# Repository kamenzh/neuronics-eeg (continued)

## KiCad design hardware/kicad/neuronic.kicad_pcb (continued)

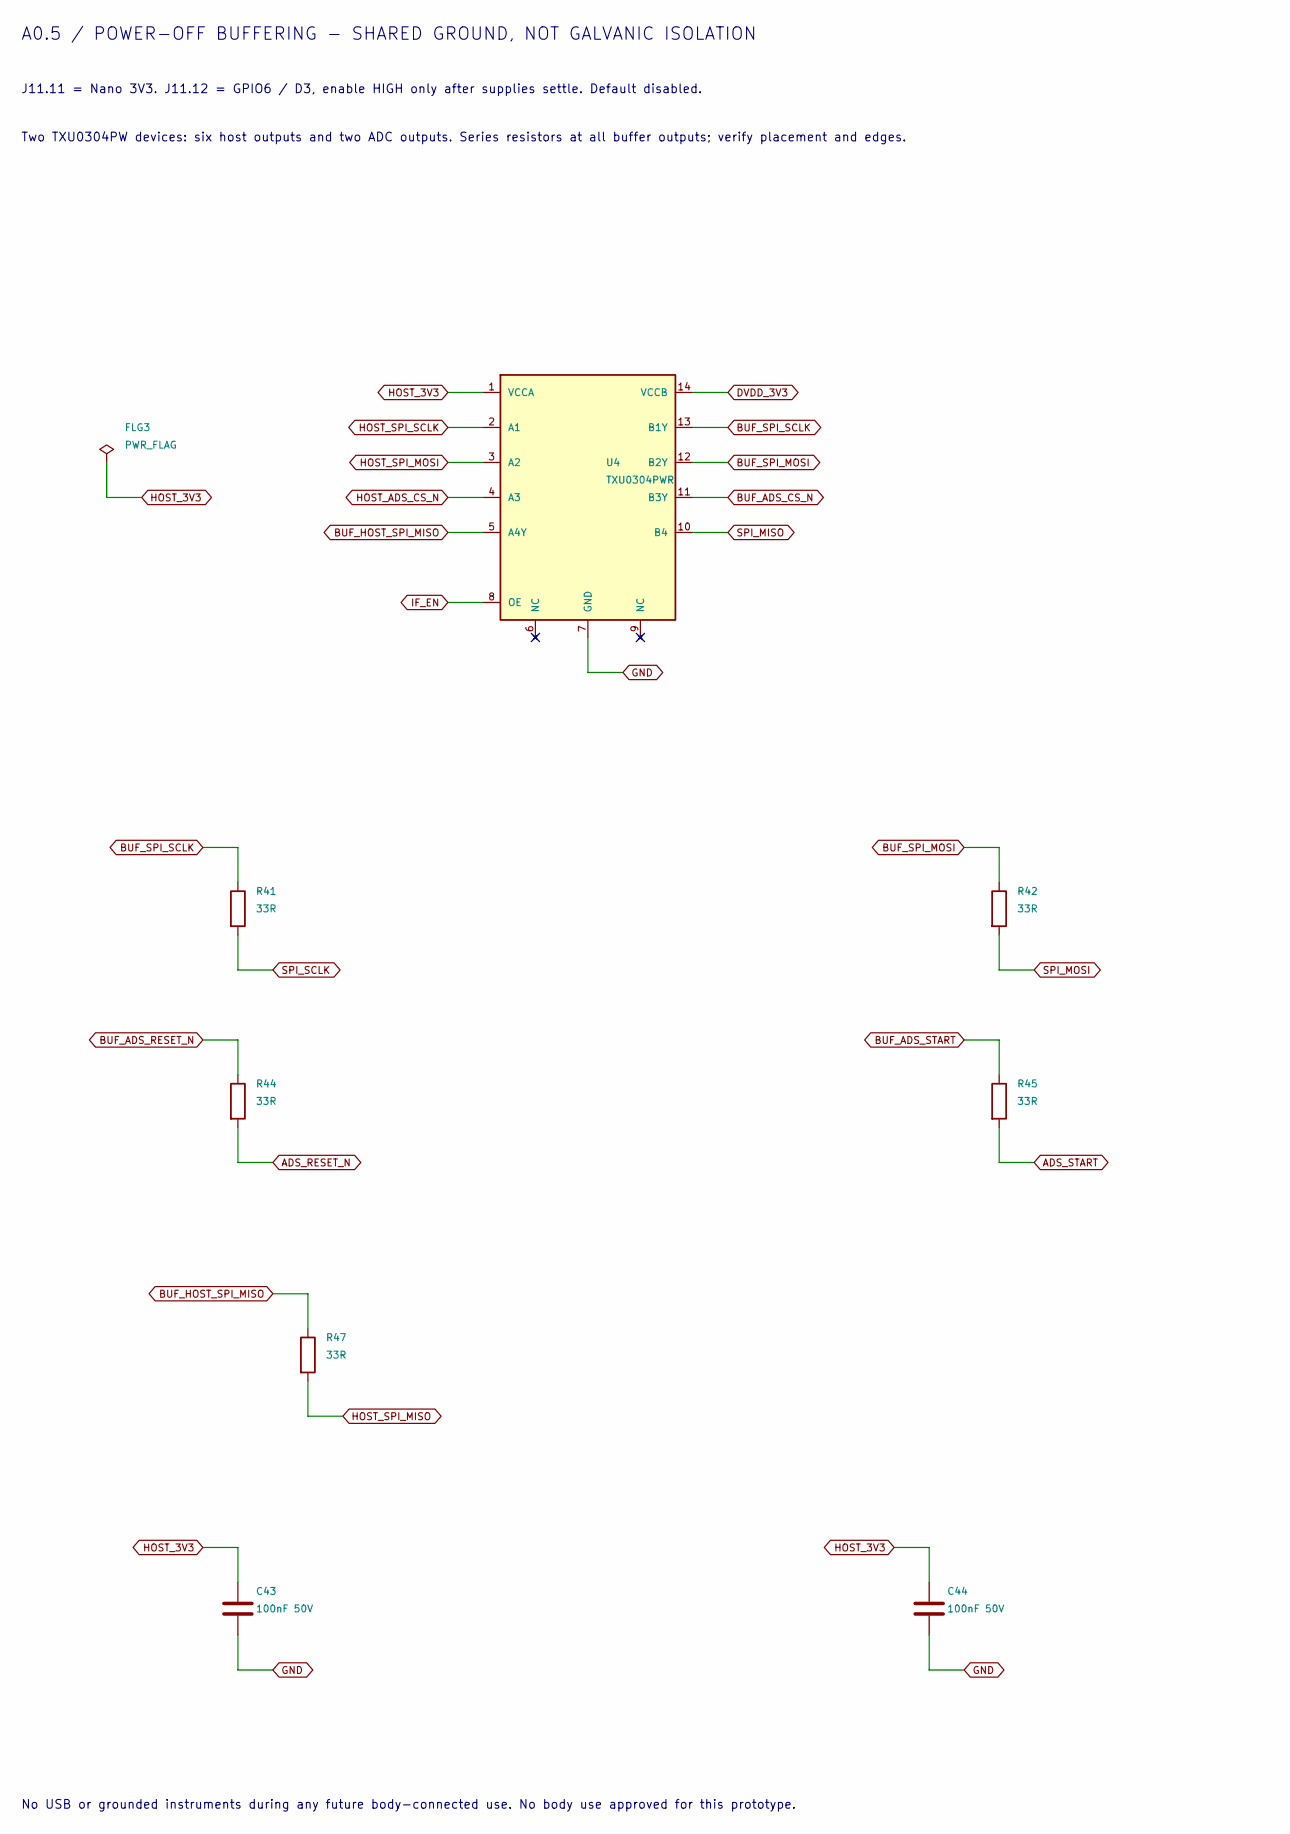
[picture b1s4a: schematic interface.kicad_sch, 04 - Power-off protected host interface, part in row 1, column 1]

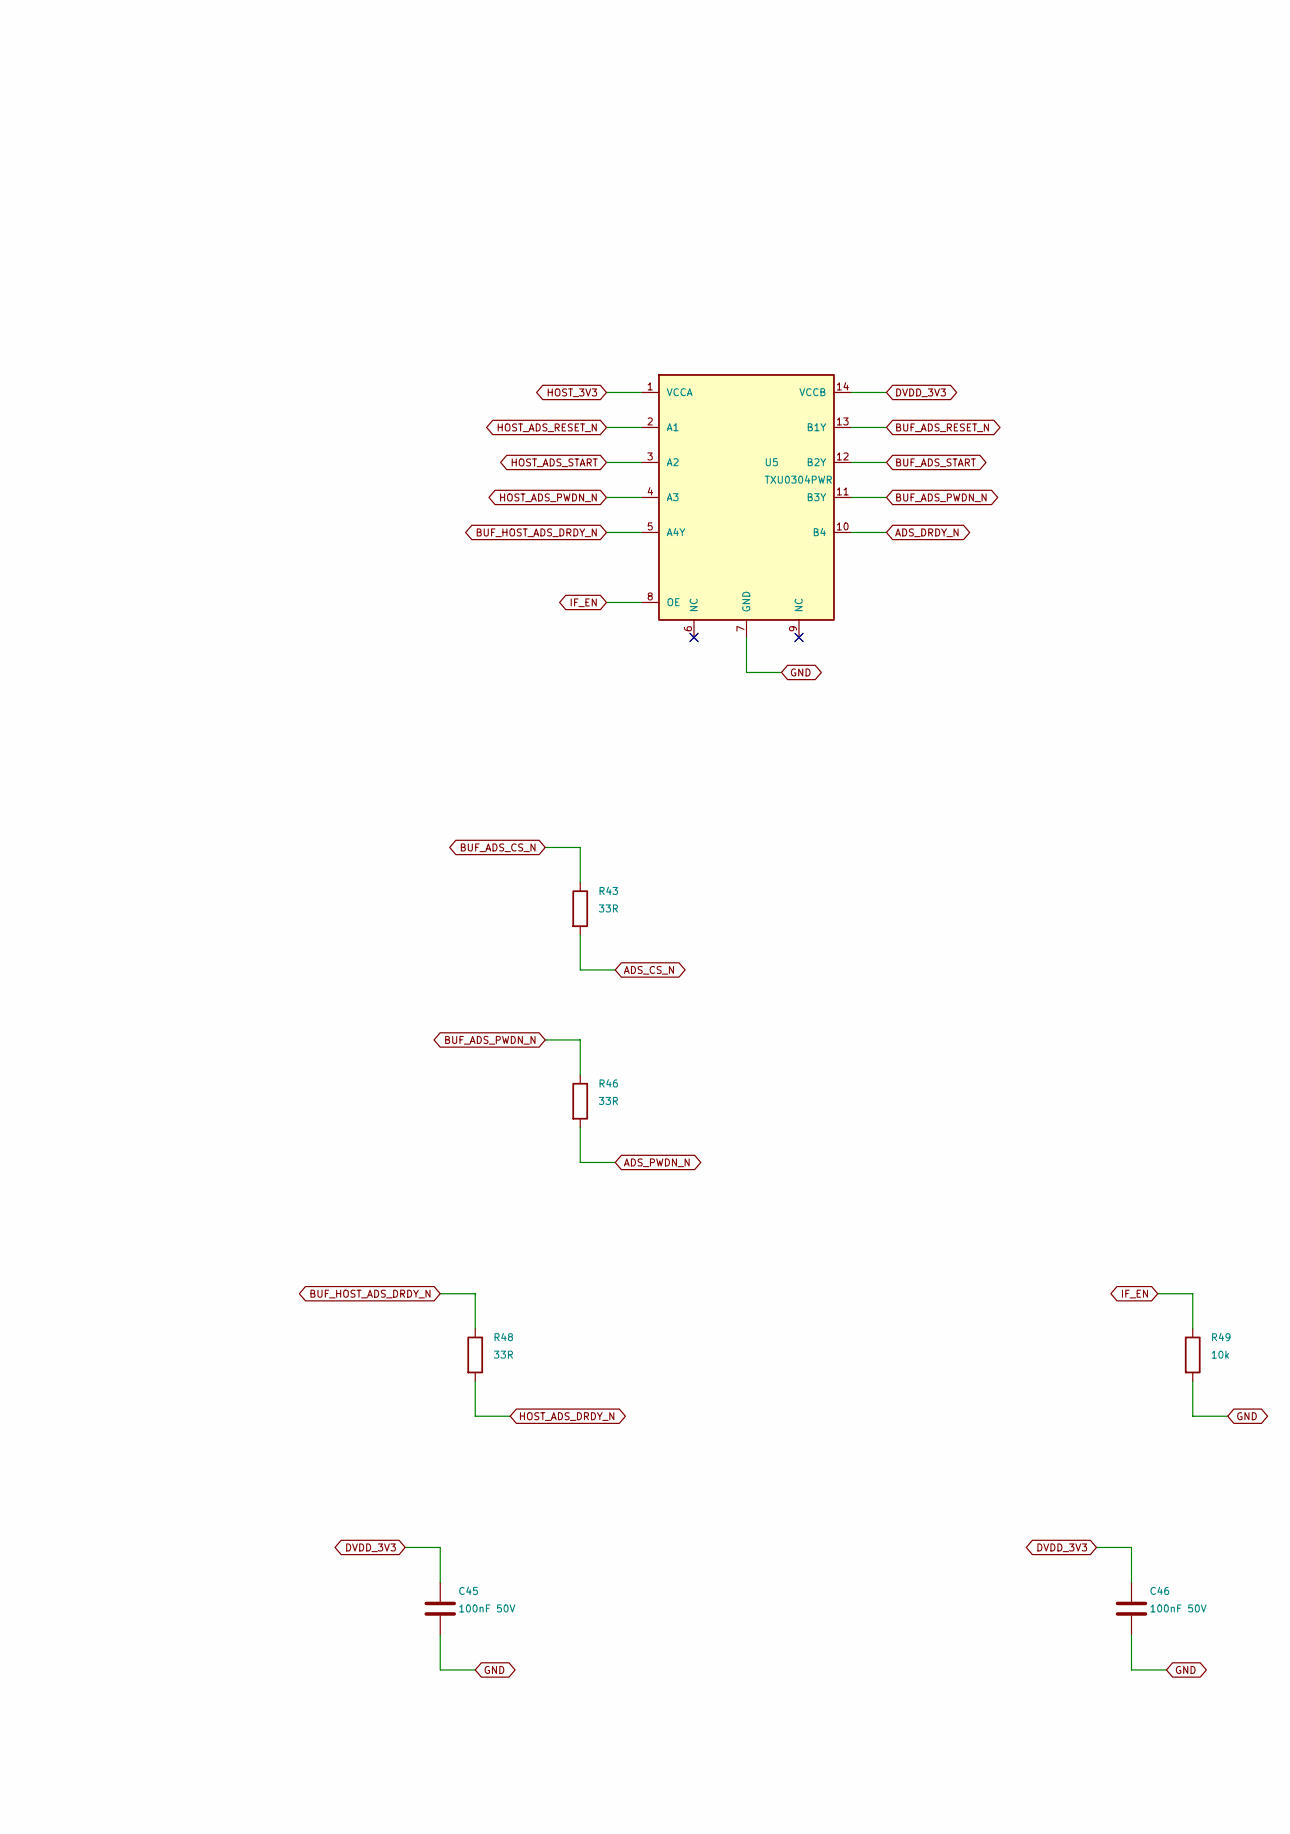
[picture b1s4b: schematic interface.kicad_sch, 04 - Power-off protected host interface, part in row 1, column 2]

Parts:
C43, C44, C45, C46: 100nF 50V; C_0805_2012Metric
FLG3: PWR_FLAG
R41, R42, R43, R44, R45, R46, R47, R48: 33R; R_0805_2012Metric
R49: 10k; R_0805_2012Metric
U4, U5: TXU0304PWR; TSSOP-14_4.4x5mm_P0.65mm

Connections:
ADS_CS_N: R43.2; also elsewhere on the board
ADS_DRDY_N: U5.10 (B4); also elsewhere on the board
ADS_PWDN_N: R46.2; also elsewhere on the board
ADS_RESET_N: R44.2; also elsewhere on the board
ADS_START: R45.2; also elsewhere on the board
BUF_ADS_CS_N: R43.1, U4.11 (B3Y)
BUF_ADS_PWDN_N: R46.1, U5.11 (B3Y)
BUF_ADS_RESET_N: R44.1, U5.13 (B1Y)
BUF_ADS_START: R45.1, U5.12 (B2Y)
BUF_HOST_ADS_DRDY_N: R48.1, U5.5 (A4Y)
BUF_HOST_SPI_MISO: R47.1, U4.5 (A4Y)
BUF_SPI_MOSI: R42.1, U4.12 (B2Y)
BUF_SPI_SCLK: R41.1, U4.13 (B1Y)
DVDD_3V3: C45.1, C46.1, U4.14 (VCCB), U5.14 (VCCB); also elsewhere on the board
GND: C43.2, C44.2, C45.2, C46.2, R49.2, U4.7 (GND), U5.7 (GND); also elsewhere on the board
HOST_3V3: C43.1, C44.1, FLG3.1, U4.1 (VCCA), U5.1 (VCCA); also elsewhere on the board
HOST_ADS_CS_N: U4.4 (A3); also elsewhere on the board
HOST_ADS_DRDY_N: R48.2; also elsewhere on the board
HOST_ADS_PWDN_N: U5.4 (A3); also elsewhere on the board
HOST_ADS_RESET_N: U5.2 (A1); also elsewhere on the board
HOST_ADS_START: U5.3 (A2); also elsewhere on the board
HOST_SPI_MISO: R47.2; also elsewhere on the board
HOST_SPI_MOSI: U4.3 (A2); also elsewhere on the board
HOST_SPI_SCLK: U4.2 (A1); also elsewhere on the board
IF_EN: R49.1, U4.8 (OE), U5.8 (OE); also elsewhere on the board
SPI_MISO: U4.10 (B4); also elsewhere on the board
SPI_MOSI: R42.2; also elsewhere on the board
SPI_SCLK: R41.2; also elsewhere on the board

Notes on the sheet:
A0.5 / POWER-OFF BUFFERING - SHARED GROUND, NOT GALVANIC ISOLATION
J11.11 = Nano 3V3. J11.12 = GPIO6 / D3, enable HIGH only after supplies settle. Default disabled.
Two TXU0304PW devices: six host outputs and two ADC outputs. Series resistors at all buffer outputs; verify placement and edges.
No USB or grounded instruments during any future body-connected use. No body use approved for this prototype.

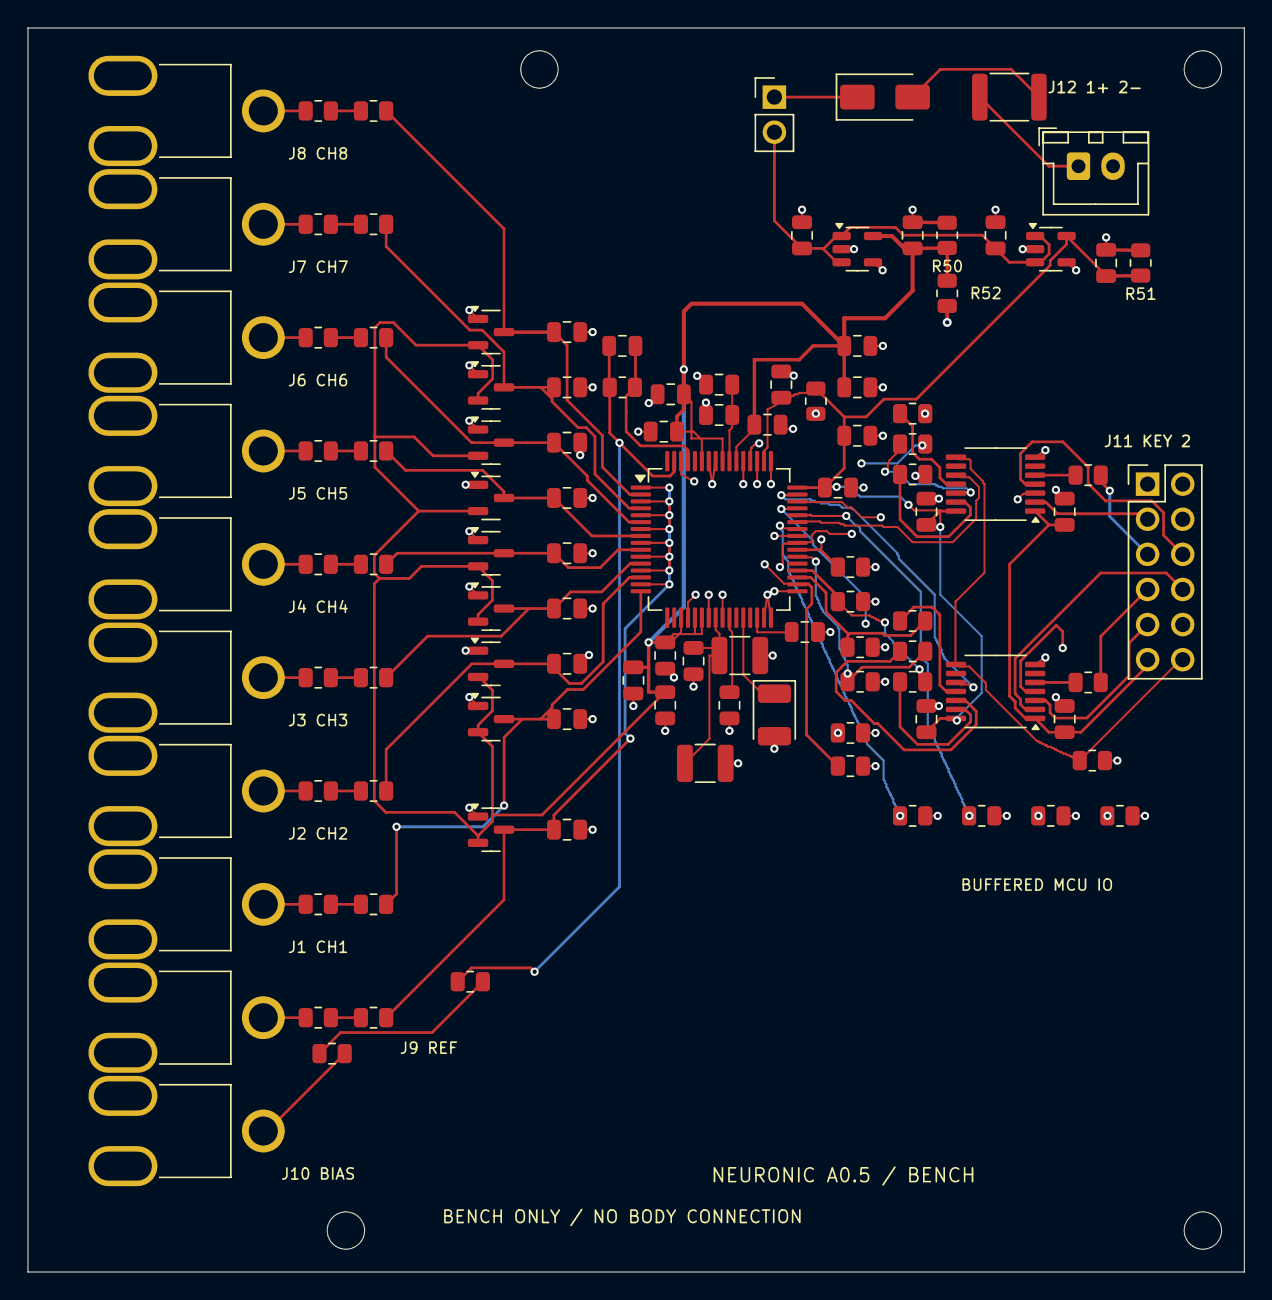
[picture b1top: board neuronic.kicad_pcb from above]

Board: 4 copper layers, 88.0 x 90.0 mm, 114 parts (0 on the bottom side), 74 nets.

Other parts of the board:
H1, H2, H3, H4: M2.5; MountingHole_2.7mm_M2.5

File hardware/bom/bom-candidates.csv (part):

References,Quantity,Manufacturer,Candidate_MPN,Specification,Footprint,Source,Review_status,Notes
R36 R37 R38 R39 R40,5,Yageo,RC0805FR-0710KL,"10 kohm, 1%, 0805, 0.125W",Neuronic:R_0805_2012Metric,https://yageogroup.com/component-documentation/download/spec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,candidate_not_order_release,Check pulse/fault stress and excess noise in final analog design
R30 R31 R32 R33 R34 R35,6,Yageo,RC0805FR-0710KL,"10k, 1%, 0805, 0.125W",Neuronic:R_0805_2012Metric,https://yageogroup.com/component-documentation/download/spec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,candidate_not_order_release,10k gives <=0.122V for 12uA combined ADC/buffer leakage; verify host startup and rail sequencing
R20,1,Yageo,RC0805FR-071ML,"1 Mohm, 1%, 0805, 0.125W",Neuronic:R_0805_2012Metric,https://yageogroup.com/component-documentation/download/spec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,candidate_not_order_release,Check pulse/fault stress and excess noise in final analog design
R21 R22,2,Yageo,RC0805FR-07499KL,"499 kohm, 1%, 0805, 0.125W",Neuronic:R_0805_2012Metric,https://yageogroup.com/component-documentation/download/spec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,candidate_not_order_release,Check pulse/fault stress and excess noise in final analog design
C10,1,KEMET,C0805C152J5GACTU,"1.5nF, 5%, 50V, C0G, 0805",Neuronic:C_0805_2012Metric,https://search.kemet.com/component-documentation/download/sp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,candidate_not_order_release,Verify effective capacitance at operating bias/temperature and aging; nominal value alone is insufficient
C25 C26 C28 C31 C32 C33 C34 C35 C36 C39 C40,11,KEMET,C0805C105K3RACTU,"1uF, 10%, 25V, X7R, 0805",Neuronic:C_0805_2012Metric,https://search.kemet.com/component-documentation/download/sp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,candidate_not_order_release,Verify effective capacitance at operating bias/temperature and aging; nominal value alone is insufficient
C27 C30 C38 C41 C43 C44 C45 C46,8,KEMET,C0805C104K5RACTU,"100nF, 10%, 50V, X7R, 0805",Neuronic:C_0805_2012Metric,https://search.kemet.com/component-documentation/download/sp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,candidate_not_order_release,Verify effective capacitance at operating bias/temperature and aging; nominal value alone is insufficient
C20 C22 C23 C21,4,KEMET,C0805C475K3RACTU,"4.7uF, 10%, 25V, X7R, 0805",Neuronic:C_0805_2012Metric,https://search.kemet.com/component-documentation/download/sp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,candidate_not_order_release,Verify effective capacitance at operating bias/temperature and aging; nominal value alone is insufficient
C37,1,KEMET,C0805C106K3PACTU,"10uF, 10%, 25V, X5R, 0805",Neuronic:C_0805_2012Metric,https://search.kemet.com/component-documentation/download/sp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,candidate_not_order_release,Verify effective capacitance at operating bias/temperature and aging; nominal value alone is insufficient
C29 C42,2,KEMET,C1210C226K3RACTU,"22uF, 10%, 25V X7R, 1210; two fitted in parallel",Neuronic:C_1210_3225Metric,https://search.kemet.com/component-documentation/download/sp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,candidate_not_order_release,Two fitted. Manufacturer typical DC-bias curve inspected; bounded design estimate >20uF combined. Physical operating-value/startup verification still required.
C24,1,KEMET,T491B107M006AT,"100uF, 20%, 6.3V, tantalum, B/3528-21",Neuronic:CP_EIA-3528-21_Kemet-B,https://search.kemet.com/component-documentation/download/sp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,candidate_not_order_release,Polarized: pad1 VCAP1 positive; verify leakage/startup/surge and derating for this internal rail
U1,1,Texas Instruments,ADS1299IPAG,"8 channels, TQFP64/PAG, 0.5mm pitch",Neuronic:TQFP-64_10x10mm_P0.5mm,https://www.ti.com/lit/ds/symlink/ads1299.pdf,candidate_not_order_release,ADS1299IPAGR is reel packaging of the same PAG device; one IC total
U2,1,Texas Instruments,TPS7A2450DBVR,"5 V fixed, 18 V input, 200 mA, SOT-23-5",Neuronic:SOT-23-5,https://www.ti.com/lit/ds/symlink/tps7a24.pdf,candidate_not_order_release,"Pin 1 IN, 2 GND, 3 EN tied to IN, 4 NC tied GND for thermal performance, 5 OUT. 2% combined accuracy budget. Measure rail noise/startup/reverse-current behavior."
U3,1,Texas Instruments,TPS7A2433DBVR,"3.3 V fixed, 18 V input, 200 mA, SOT-23-5",Neuronic:SOT-23-5,https://www.ti.com/lit/ds/symlink/tps7a24.pdf,candidate_not_order_release,"Pin 1 IN, 2 GND, 3 EN tied to IN, 4 NC tied GND for thermal performance, 5 OUT. 2% combined accuracy budget. Measure rail noise/startup/reverse-current behavior."
D1 D2 D3 D4 D5 D6 D7 D8 D9,9,Nexperia,"BAV199,215","Dual series low leakage diode, SOT-23",Neuronic:SOT-23,https://assets.nexperia.com/documents/data-sheet/BAV199.pdf,candidate_not_order_release,Not a proven ADS1299 absolute-maximum clamp or body-protection solution
D10,1,Vishay,SS14-E3/61T,"40V, 1A Schottky, SMA",Neuronic:D_SMA,https://www.vishay.com/docs/88746/ss12.pdf,candidate_not_order_release,Check forward drop at AFE load and reverse leakage
F1,1,Bourns,MF-MSMF014-2,"1812, 60 V, 0.14 A hold / 0.34 A trip at 23 C",Neuronic:Fuse_1812_4532Metric,https://www.bourns.com/docs/product-datasheets/mf-msmf.pdf,candidate_not_order_release,
J12,1,JST,B2B-XH-A(LF)(SN),"2-pin, 2.50mm, vertical XH",Neuronic:JST_XH_B2B-XH-A_1x02_P2.50mm_Vertical,https://www.jst-mfg.com/product/pdf/eng/eXH.pdf,candidate_not_order_release,Harness requires matching XHP-2 housing and wire-appropriate contacts; do not infer polarity from wire color
J11,1,Wurth Elektronik,61301221121,"2x6, 2.54mm, vertical male header",Neuronic:PinHeader_2x06_P2.54mm_Vertical,https://www.we-online.com/components/products/datasheet/6130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,candidate_not_order_release,A0.5 keyed harness: pad 2 isolated. Remove exposed pin 2 and plug matching socket cavity. Only pin 1 is signal ground.
J1 J2 J3 J4 J5 J6 J7 J8 J9 J10,10,P1 Technologies,8R003661901F,36619 black right-angle PCB jack; 1.5 mm touchproof DIN 42802 Type BU,Neuronic:P1_36619_Touchproof_RA,https://catalog.p1tec.com/?FILTER_CLEAR=&FILTER_FCOMPONENT=36619,candidate_not_order_release,A0.3: signal finished hole 2.10mm; isolated dummy plated slots 4.20x2.10mm. See tolerance worksheet; sample fit and fabricator slot confirmation required.
SW1,1,Wurth Elektronik,61300211121,"1x2, 2.54mm header for offboard SPST switch",Neuronic:PinHeader_1x02_P2.54mm_Vertical,https://www.we-online.com/components/products/datasheet/6130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,candidate_not_order_release,"This MPN buys the PCB header, not the external switch"
U4 U5,2,Texas Instruments,TXU0304PWR,"3 A-to-B + 1 B-to-A buffer, dual supply, Ioff/VCC disconnect, TSSOP-14",Neuronic:TSSOP-14_4.4x5mm_P0.65mm,https://www.ti.com/lit/ds/symlink/txu0304.pdf,candidate_not_order_release,"A=host 3.3V, B=AFE 3.3V, OE controlled on J11.12. Common ground; NOT galvanic isolation."
R41 R42 R43 R44 R45 R46 R47 R48,8,Yageo,RC0805FR-0733RL,"33 ohm, 1%, 0805",Neuronic:R_0805_2012Metric,https://www.yageo.com/en/Chart/Download/pdf/RC0805.pdf,candidate_not_order_release,Source damping at buffer outputs; not a safety current limiter.
R49,1,Yageo,RC0805FR-0710KL,"10k, 1%, 0805",Neuronic:R_0805_2012Metric,https://www.yageo.com/en/Chart/Download/pdf/RC0805.pdf,candidate_not_order_release,Buffer OE default disabled.
R51,1,Yageo,RC0805FR-071KL,"1 kohm, 1%, 0805, 0.125W",Neuronic:R_0805_2012Metric,https://yageogroup.com/component-documentation/download/spec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,candidate_not_order_release,Passive regulator-output discharge load.
R1 R2 R3 R4 R5 R6 R7 R8 R9 R10 R11 R12 R13 R14 R15 R16 R17 R18,18,Yageo,RT0805BRD07100KL,"100 kohm, 0.1%, 25 ppm/K, 0805",Neuronic:R_0805_2012Metric,https://www.yageogroup.com/component-documentation/download/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,candidate_not_order_release,Two independent series resistors per contact.
R50 R52,2,Yageo,RC0805FR-07499RL,"499 ohm, 1%, 0805, 0.125 W",Neuronic:R_0805_2012Metric,https://www.yageogroup.com/component-documentation/download/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,candidate_not_order_release,"Parallel analog rail bleeds, individually rated for the full rail voltage."
C1 C2 C3 C4 C5 C6 C7 C8,8,KEMET,C0805C471F5GACTU,"470 pF, 1%, 50 V, C0G, 0805",Neuronic:C_0805_2012Metric,https://yageogroup.com/download/specsheet/C0805C471F5GACTU,candidate_not_order_release,C9 is tuned separately for the shared reference. Verify actual common-mode response.
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
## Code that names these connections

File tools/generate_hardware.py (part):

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    '23':'AVSS', '24':'VREFP', '25':'VREFN', '26':'VCAP4', '27':'NC', '28':'VCAP1',
    '29':'NC', '30':'VCAP2', '31':'RESV1', '32':'AVSS', '33':'DGND', '34':'DIN',
    '35':'~{PWDN}', '36':'~{RESET}', '37':'CLK', '38':'START', '39':'~{CS}', '40':'SCLK',
    '41':'DAISY_IN', '42':'GPIO1', '43':'DOUT', '44':'GPIO2', '45':'GPIO3', '46':'GPIO4',
    '47':'~{DRDY}', '48':'DVDD', '49':'DGND', '50':'DVDD', '51':'DGND', '52':'CLKSEL',
    '53':'AVSS1', '54':'AVDD1', '55':'VCAP3', '56':'AVDD', '57':'AVSS', '58':'AVSS',
    '59':'AVDD', '60':'BIASREF', '61':'BIASINV', '62':'BIASIN', '63':'BIASOUT', '64':'RESERVED'}
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        typ = 'input'
        if name.startswith(('AVDD','AVSS','DVDD','DGND')): typ='power_in'
        elif name in ['DOUT','~{DRDY}','BIASOUT'] or name.startswith('VCAP'): typ='output'
        elif name.startswith('GPIO') or name in ['SRB1','SRB2','VREFP','BIASINV']: typ='bidirectional'
        elif name in ['NC','RESERVED']: typ='no_connect'
        pins.append((str(i), name, typ, -22.86 if side else 22.86, y, 0 if side else 180))
    LIB['Neuronic:ADS1299IPAG'] = custom_symbol('ADS1299IPAG', pins, 20.32, 43.18,
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    nets.update({'17':None,'18':None,'19':'AVDD_5V','20':'GND','21':'AVDD_5V','22':'AVDD_5V','23':'GND',
        '24':'VREFP','25':'GND','26':'VCAP4','27':None,'28':'VCAP1','29':None,'30':'VCAP2','31':'GND','32':'GND',
        '33':'GND','34':'SPI_MOSI','35':'ADS_PWDN_N','36':'ADS_RESET_N','37':None,'38':'ADS_START','39':'ADS_CS_N',
        '40':'SPI_SCLK','41':'GND','42':'GPIO1_PD','43':'SPI_MISO','44':'GPIO2_PD','45':'GPIO3_PD','46':'GPIO4_PD',
        '47':'ADS_DRDY_N','48':'DVDD_3V3','49':'GND','50':'DVDD_3V3','51':'GND','52':'CLKSEL_PU',
        '53':'GND','54':'AVDD_5V','55':'VCAP3','56':'AVDD_5V','57':'GND','58':'GND','59':'AVDD_5V',
        '60':None,'61':'BIASINV','62':'GND','63':'BIASOUT','64':None})
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    root.text('Waveshare ESP32-S3-Nano; see hardware/interface.json.',258,100)
    root.text('External controller power/USB can join GND. No body-connected tests.',258,107)
    rnum=30
    for i,(net,rail) in enumerate([('ADS_CS_N','GND'),('ADS_RESET_N','GND'),('ADS_PWDN_N','GND'),('ADS_START','GND'),('SPI_SCLK','GND'),('SPI_MOSI','GND'),('CLKSEL_PU','DVDD_3V3'),('GPIO1_PD','GND'),('GPIO2_PD','GND'),('GPIO3_PD','GND'),('GPIO4_PD','GND')]):
        x=35+(i%6)*58;y=181+(i//6)*40
        add_rc(root,f'R{rnum+i}','10k',net,rail,x,y,(116+(i%4)*5,103+(i//4)*7))
    root.text('Default pulldowns keep ADC controls low at startup. MCU must release PWDN/RESET and drive CS high after rails settle.',20,250)
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
    power.text('BENCH POWER: 6 x AA alkaline candidate (7.2-10.2 V review envelope) -> 5 V / 3.3 V LDOs',18,17,1.8)
    power.text('ESP32 has its own supply. No onboard charging. Regulators must not supply ESP32 radio current.',18,25)
    power.part('J12','Connector_Generic:Conn_01x02','BATTERY_6AA',40,48,{'1':'VBAT_RAW','2':'GND'},'Neuronic:JST_XH_B2B-XH-A_1x02_P2.50mm_Vertical',xy=(132,66),note='Candidate keyed battery connector; pin 1 positive, pin 2 ground; verify harness polarity')
    power.part('F1','Device:Polyfuse','140mA_HOLD',100,48,{'1':'VBAT_RAW','2':'VBAT_FUSED'},'Neuronic:Fuse_1812_4532Metric',xy=(124,60),note='MF-MSMF014-2: 60V, 140mA hold / 340mA trip at 23C; AFE branch only, not body protection',mpn='MF-MSMF014-2')
    power.part('D10','Device:D_Schottky','SS14',162,48,{'2':'VBAT_FUSED','1':'VBAT_DIODE'},'Neuronic:D_SMA',xy=(117,60),note='Reverse polarity protection; verify thermal behavior',mpn='SS14')
    power.part('SW1','Switch:SW_SPST','POWER',220,48,{'1':'VBAT_DIODE','2':'VBAT'},'Neuronic:PinHeader_1x02_P2.54mm_Vertical',xy=(109,60),note='Header for an offboard SPST switch')
    for i,(value,rail) in enumerate([('TPS7A2450DBVR','AVDD_5V'),('TPS7A2433DBVR','DVDD_3V3')]):
        power.part(f'U{i+2}','Neuronic:TPS7A24_FIXED',value,95+155*i,86,{'1':'VBAT','2':'GND','3':'VBAT','4':'GND','5':rail},'Neuronic:SOT-23-5',xy=(109+i*14,72),note='Fixed DBV: 1 VIN, 2 GND, 3 EN=VIN, 4 NC=GND, 5 VOUT',mpn=value)
    add_rc(power,'R50','499R','AVDD_5V','GND',330,86,(116.5,70),rot=90)
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
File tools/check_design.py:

#!/usr/bin/env python3
"""Audit the actual KiCad-exported netlist against the source and pin contract.

Not a replacement for ERC, DRC, analog review or physical measurements.
"""
import json
import sys
import xml.etree.ElementTree as ET
from pathlib import Path

ROOT=Path(__file__).resolve().parents[1]
src=json.loads((ROOT/'hardware/design.json').read_text())
tree=ET.parse(ROOT/'hardware/validation/neuronic.net.xml').getroot()
comps={x.attrib['ref']:x for x in tree.findall('components/comp')}
actual={}
for net in tree.findall('nets/net'):
    for node in net.findall('node'):
        actual[(node.attrib['ref'],node.attrib['pin'])]=net.attrib['name']
checks=[]
def check(name,condition):
    checks.append({'name':name,'passed':bool(condition)})
    if not condition: print('FAIL:',name)

parts={p['ref']:p for p in src['parts']}
check('All 110 physical components exported by KiCad',set(parts)==set(comps) and len(parts)==110)
for p in parts.values():
    check(f"{p['ref']} footprint matches schematic",comps[p['ref']].findtext('footprint')==p['fp'])
    for pin,net in p['nets'].items():
        found=actual.get((p['ref'],pin),'')
        check(f"{p['ref']}.{pin} -> {net or 'NC'}",found==net if net else found.startswith('unconnected-') or not found)

# This physical pin contract is deliberately independent of the generator's map.
pin_contract={
    '16':'EEG1','14':'EEG2','12':'EEG3','10':'EEG4','8':'EEG5','6':'EEG6','4':'EEG7','2':'EEG8',
    '1':'REF_FILTERED','3':'REF_FILTERED','5':'REF_FILTERED','7':'REF_FILTERED',
    '9':'REF_FILTERED','11':'REF_FILTERED','13':'REF_FILTERED','15':'REF_FILTERED',
    '24':'VREFP','25':'GND','26':'VCAP4','28':'VCAP1','30':'VCAP2',
    '31':'GND','33':'GND','34':'SPI_MOSI','35':'ADS_PWDN_N','36':'ADS_RESET_N',
    '38':'ADS_START','39':'ADS_CS_N','40':'SPI_SCLK','41':'GND','43':'SPI_MISO',
    '47':'ADS_DRDY_N','48':'DVDD_3V3','49':'GND','50':'DVDD_3V3','51':'GND',
    '52':'CLKSEL_PU','53':'GND','54':'AVDD_5V','55':'VCAP3','61':'BIASINV','62':'GND','63':'BIASOUT'}
for pin,net in pin_contract.items():check(f'TI pin contract U1.{pin}',actual.get(('U1',pin))==net)
for pin in ['19','21','22','56','59']:check(f'Analog rail U1.{pin}',actual.get(('U1',pin))=='AVDD_5V')
for pin in ['20','23','32','57','58']:check(f'Analog return U1.{pin}',actual.get(('U1',pin))=='GND')
for ref,rail in [('U2','AVDD_5V'),('U3','DVDD_3V3')]:
    for pin,net in {'1':'VBAT','2':'GND','3':'VBAT','4':'GND','5':rail}.items():
        check(f'TI fixed TPS7A24 DBV contract {ref}.{pin}',actual.get((ref,pin))==net)
    check(f'{ref} uses SOT-23-5 footprint',comps[ref].findtext('footprint')=='Neuronic:SOT-23-5')
for i in range(1,19):
    check(f'Contact series resistor R{i}', comps[f'R{i}'].findtext('value') == '100k')
for i in range(1,10):
    check(f'Input shunt C{i}', comps[f'C{i}'].findtext('value') == ('470pF C0G' if i<9 else '330pF C0G'))
for ref, rail in [('R50','AVDD_5V'),('R51','DVDD_3V3'),('R52','AVDD_5V')]:
    check(f'{ref} regulator discharge path', comps[ref].findtext('value')==('1k' if ref=='R51' else '499R') and actual.get((ref,'1'))==rail and actual.get((ref,'2'))=='GND')
for i in range(1,11):
    check(f'J{i} selected touchproof jack footprint',comps[f'J{i}'].findtext('footprint')=='Neuronic:P1_36619_Touchproof_RA')
for i in range(1,10):
    check(f'Clamp D{i}: A1=GND / K2=5V / midpoint=signal',
      actual.get((f'D{i}','1'))=='GND' and actual.get((f'D{i}','2'))=='AVDD_5V' and
      actual.get((f'D{i}','3'))==(f'EEG{i}' if i<9 else 'REF_FILTERED'))
check('J11 key pin is an explicit NC', actual.get(('J11','2'),'').startswith('unconnected-'))
check('F1 updated PTC', comps['F1'].findtext('value')=='140mA_HOLD' and parts['F1']['mpn']=='MF-MSMF014-2')
check('J11 pin 11 powers buffer host ports only',actual.get(('J11','11'))=='HOST_3V3')
check('J11 pin 12 is interface enable',actual.get(('J11','12'))=='IF_EN')
buffer_contract={
 'U4':{'1':'HOST_3V3','2':'HOST_SPI_SCLK','3':'HOST_SPI_MOSI','4':'HOST_ADS_CS_N',
       '5':'BUF_HOST_SPI_MISO','7':'GND','8':'IF_EN','10':'SPI_MISO',
       '11':'BUF_ADS_CS_N','12':'BUF_SPI_MOSI','13':'BUF_SPI_SCLK','14':'DVDD_3V3'},
 'U5':{'1':'HOST_3V3','2':'HOST_ADS_RESET_N','3':'HOST_ADS_START','4':'HOST_ADS_PWDN_N',
       '5':'BUF_HOST_ADS_DRDY_N','7':'GND','8':'IF_EN','10':'ADS_DRDY_N',
       '11':'BUF_ADS_PWDN_N','12':'BUF_ADS_START','13':'BUF_ADS_RESET_N','14':'DVDD_3V3'}}
for ref,contract in buffer_contract.items():
    for pin,net in contract.items():check(f'TI TXU0304 PW contract {ref}.{pin}',actual.get((ref,pin))==net)
    for pin in ['6','9']:check(f'{ref}.{pin} NC',actual.get((ref,pin),'').startswith('unconnected-'))
for ref in ['R30','R31','R32','R33','R34','R35','R49']:
    check(f'{ref} 10k default-low value',comps[ref].findtext('value')=='10k')
check('Two parallel reference bulk capacitors',all(actual.get((r,'1'))=='VREFP' and actual.get((r,'2'))=='GND' for r in ['C29','C42']))
for pin in ['17','18']:
    check(f'Unused SRB pin {pin} is NC',actual.get(('U1',pin),'').startswith('unconnected-'))
interface=json.loads((ROOT/'hardware/interface.json').read_text())
for entry in interface['j11']:
    if entry['net']:
        check(f"Controller header J11.{entry['pin']}",actual.get(('J11',str(entry['pin'])))==entry['net'])
gpios=[p['gpio'] for p in interface['j11'] if p['gpio'] is not None]
check('Nine distinct controller signals including enable',len(gpios)==len(set(gpios))==9)
check('No reserved GPIO used',not(set(gpios)&set(interface['controller']['reserved_gpio'])))
native_contract={3:(5,'D2'),4:(38,'D11'),5:(47,'D12'),6:(21,'D10'),7:(18,'D9'),8:(17,'D8'),9:(10,'D7'),10:(9,'D6'),12:(6,'D3')}
for entry in interface['j11']:
    if entry['pin'] in native_contract:
        check(f"Verified Nano label/GPIO J11.{entry['pin']}",(entry['gpio'],entry['board_label'])==native_contract[entry['pin']])
check('Direct shared reference firmware contract',interface['acquisition']['misc1']==0 and not interface['acquisition']['srb2_enabled'])
check('VCAP1 polarized capacitor orientation',actual.get(('C24','1'))=='VCAP1' and actual.get(('C24','2'))=='GND')
check('Bias feedback resistor and capacitor are in parallel',
      actual[('R20','1')]==actual[('C10','1')]=='BIASOUT' and actual[('R20','2')]==actual[('C10','2')]=='BIASINV')
result={'passed':sum(x['passed'] for x in checks),'total':len(checks),'checks':checks,
  'scope':'KiCad-exported connectivity and footprint audit. Does not prove electrical behavior or safety.'}
(ROOT/'hardware/validation/connectivity-checks.json').write_text(json.dumps(result,indent=2)+'\n')
print(f"Connectivity checks: {result['passed']}/{result['total']}")
sys.exit(0 if result['passed']==result['total'] else 1)
